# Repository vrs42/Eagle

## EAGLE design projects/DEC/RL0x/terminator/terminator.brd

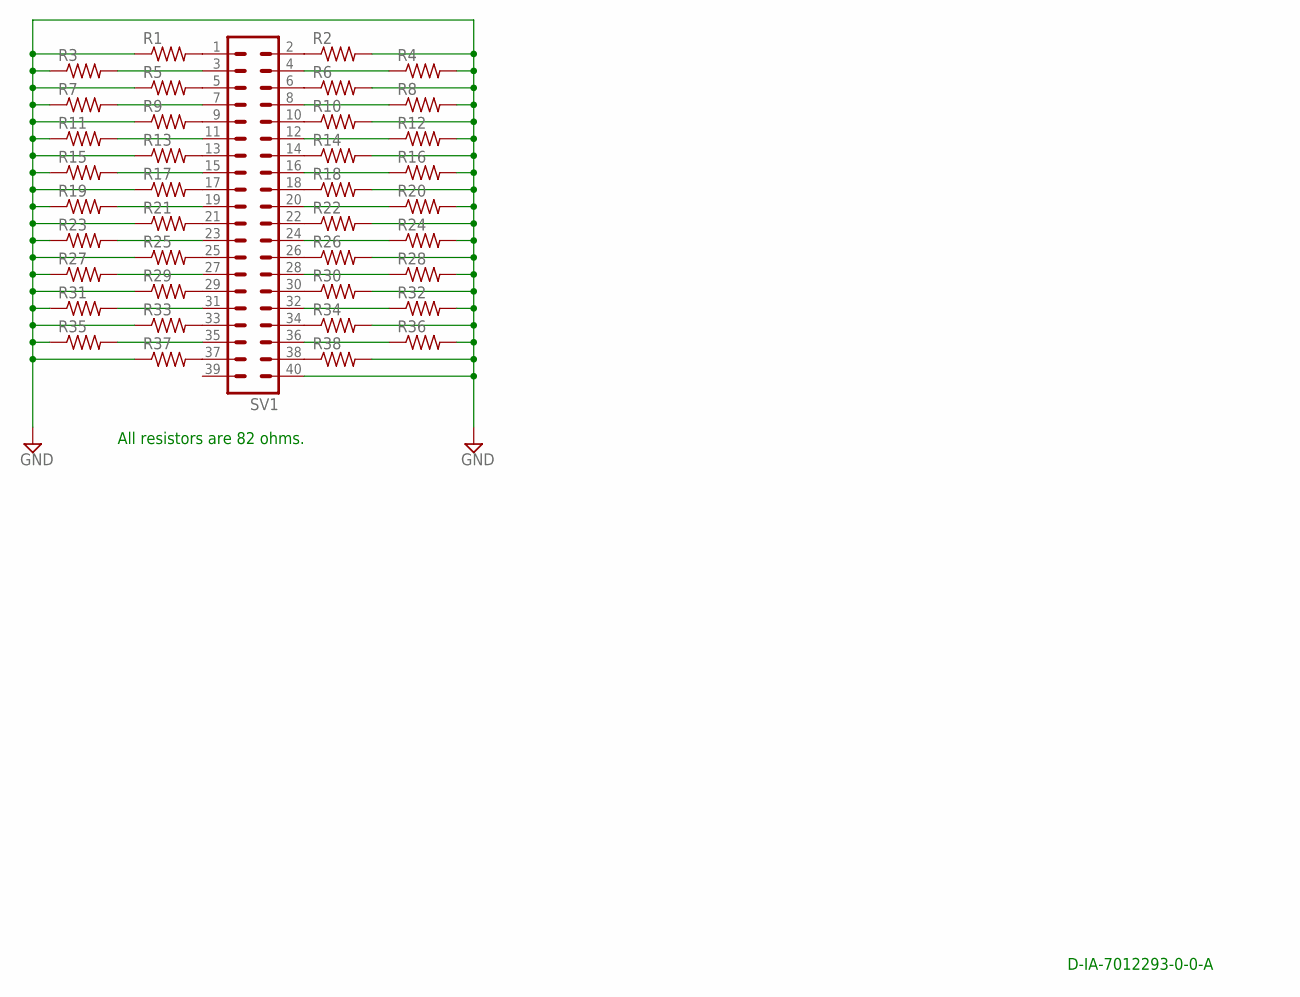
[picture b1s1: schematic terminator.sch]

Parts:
R1, R2, R3, R4, R5, R6, R7, R8, R9, R10, R11, R12, R13, R14, R15, R16, R17, R18, R19, R20, R21, R22, R23, R24, R25, R26, R27, R28, R29, R30, R31, R32, R33, R34, R35, R36, R37, R38: R-US_M0805; M0805
SV1: MA20-2

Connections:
GND: R1.1, R2.2, R3.1, R4.2, R5.1, R6.2, R7.1, R8.2, R9.1, R10.2, R11.1, R12.2, R13.1, R14.2, R15.1, R16.2, R17.1, R18.2, R19.1, R20.2, R21.1, R22.2, R23.1, R24.2, R25.1, R26.2, R27.1, R28.2, R29.1, R30.2, R31.1, R32.2, R33.1, R34.2, R35.1, R36.2, R37.1, R38.2, SV1.40
unnamed: R1.2, SV1.1
unnamed: R2.1, SV1.2
unnamed: R5.2, SV1.5
unnamed: R6.1, SV1.6
unnamed: R9.2, SV1.9
unnamed: R10.1, SV1.10
unnamed: R13.2, SV1.13
unnamed: R14.1, SV1.14
unnamed: R17.2, SV1.17
unnamed: R18.1, SV1.18
unnamed: R21.2, SV1.21
unnamed: R22.1, SV1.22
unnamed: R25.2, SV1.25
unnamed: R26.1, SV1.26
unnamed: R29.2, SV1.29
unnamed: R30.1, SV1.30
unnamed: R33.2, SV1.33
unnamed: R34.1, SV1.34
unnamed: R37.2, SV1.37
unnamed: R38.1, SV1.38
unnamed: R3.2, SV1.3
unnamed: R7.2, SV1.7
unnamed: R11.2, SV1.11
unnamed: R15.2, SV1.15
unnamed: R19.2, SV1.19
unnamed: R23.2, SV1.23
unnamed: R27.2, SV1.27
unnamed: R31.2, SV1.31
unnamed: R35.2, SV1.35
unnamed: R36.1, SV1.36
unnamed: R32.1, SV1.32
unnamed: R28.1, SV1.28
unnamed: R24.1, SV1.24
unnamed: R20.1, SV1.20
unnamed: R16.1, SV1.16
unnamed: R12.1, SV1.12
unnamed: R8.1, SV1.8
unnamed: R4.1, SV1.4

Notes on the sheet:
All resistors are 82 ohms.
D-IA-7012293-0-0-A

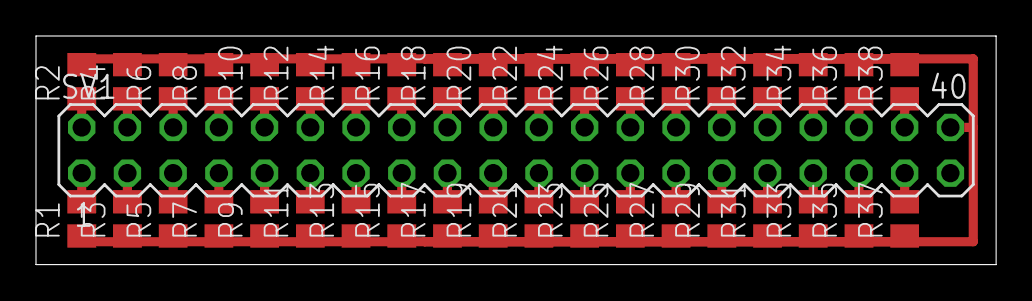
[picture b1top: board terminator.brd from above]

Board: 2 copper layers, 53.3 x 12.7 mm, 39 parts (0 on the bottom side), 39 nets.

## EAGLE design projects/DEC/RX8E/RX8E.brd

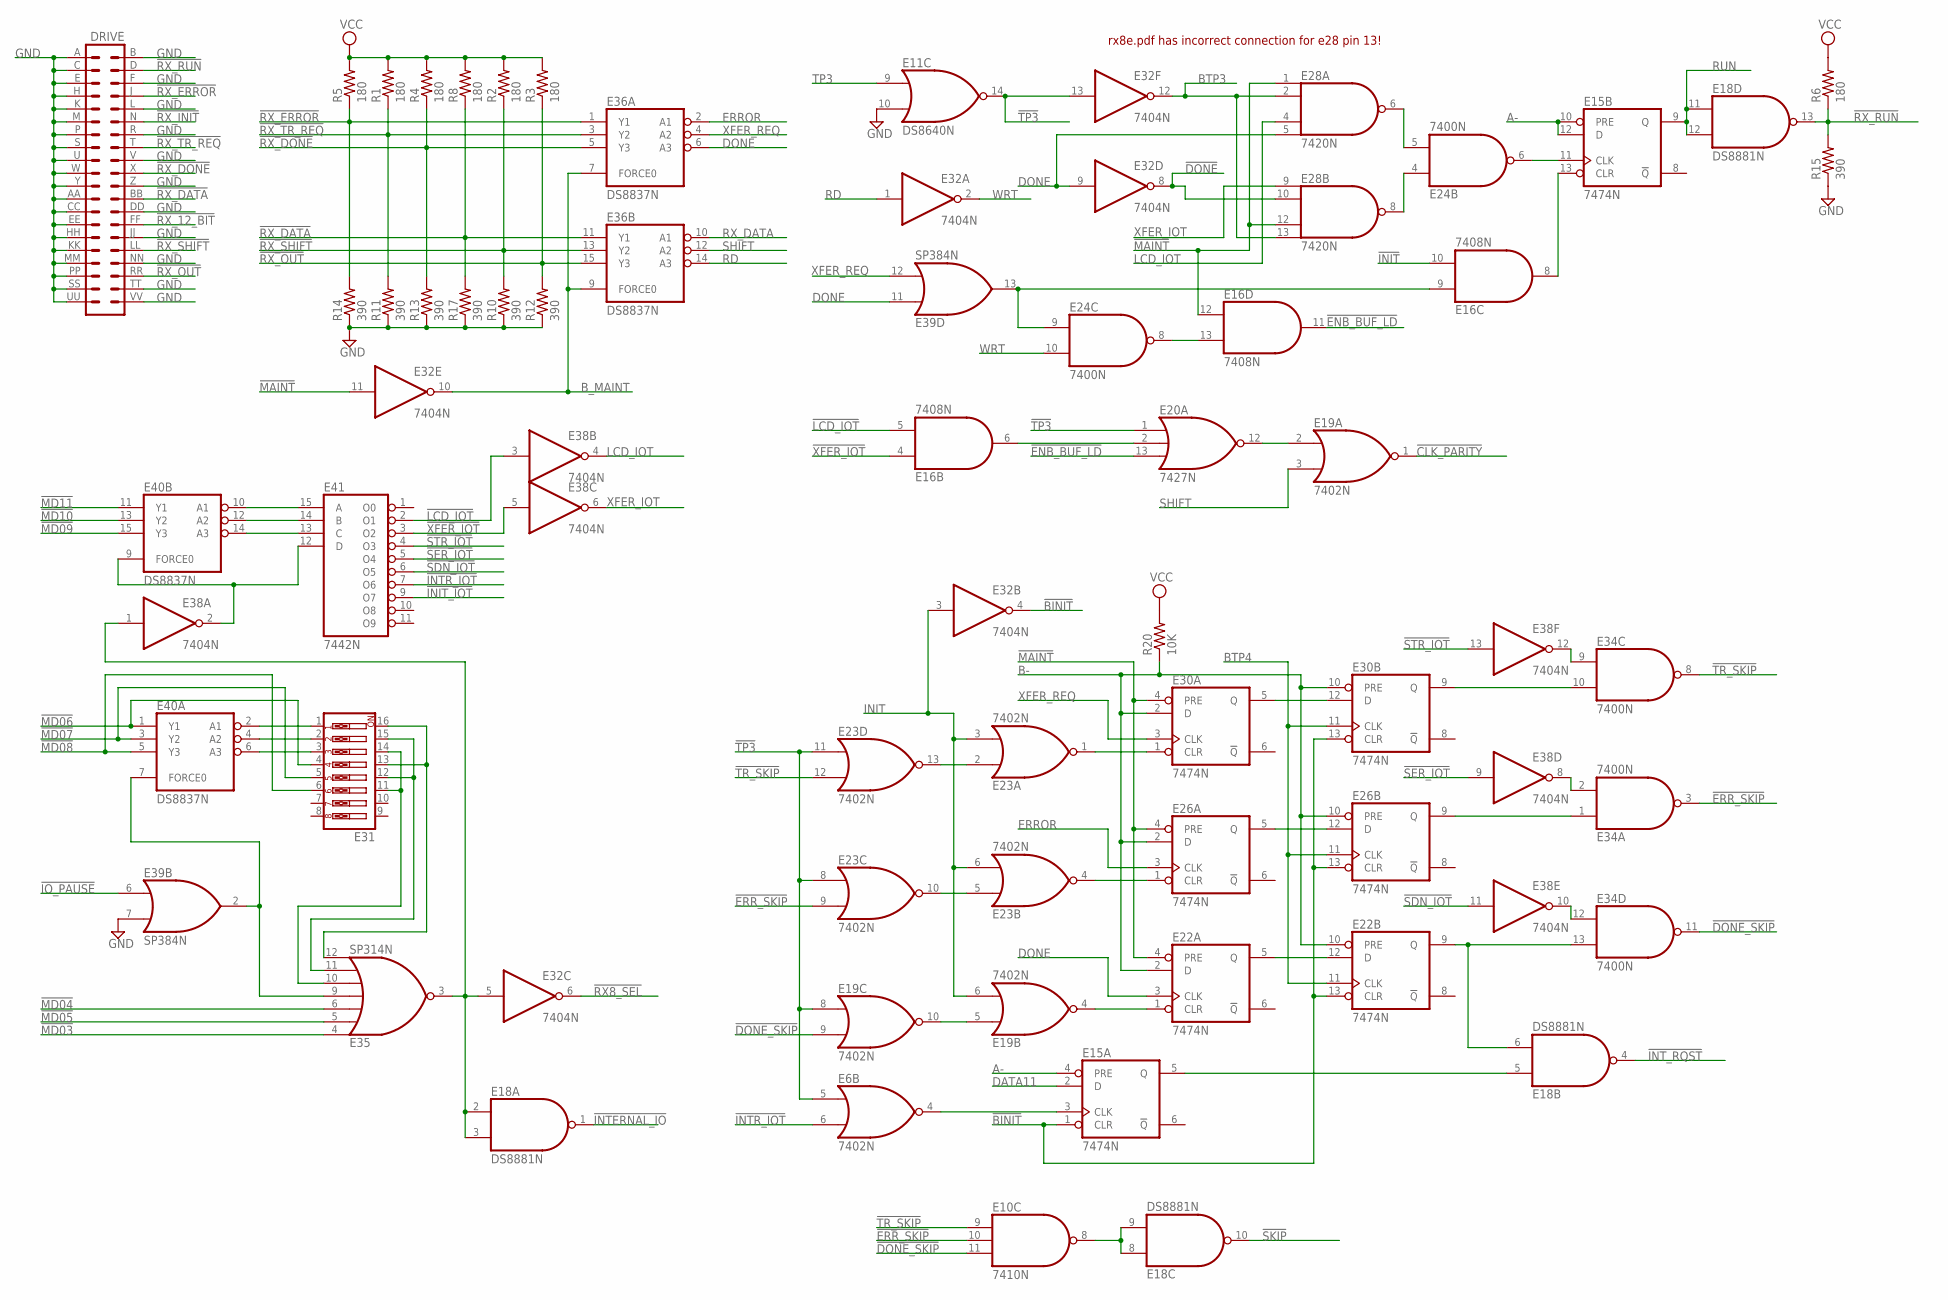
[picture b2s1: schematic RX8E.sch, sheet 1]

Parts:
DRIVE: DEC40PINH
E6, E19, E23: 7402N; DIL14
E10: 7410N; DIL14
E11: DS8640N; DIL14
E15, E22, E26, E30: 7474N; DIL14
E16: 7408N; DIL14
E18: DS8881N; DIL14
E20: 7427N; DIL14
E24, E34: 7400N; DIL14
E28: 7420N; DIL14
E31: SW_DIP-8; EDG-08
E32, E38: 7404N; DIL14
E35: SP314N; DIL14
E36, E40: DS8837N; DIL16
E39: SP384N; DIL14
E41: 7442N; DIL16
R1, R2, R3, R4, R5, R6, R8: 180; 0207/10
R10, R11, R12, R13, R14, R15, R17: 390; 0207/10
R20: 10K; 0207/10

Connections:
!BINIT: E15.1 (CLR), E22.13 (CLR), E26.13 (CLR), E30.13 (CLR), E32.4 (O)
!CLK_PARITY: E19.1 (O); also elsewhere on the board
!DONE: E28.10 (I1), E32.8 (O); also elsewhere on the board
!DONE_SKIP: E10.11 (I2), E19.9 (I1), E34.11 (O); also elsewhere on the board
!ENB_BUF_LD: E16.11 (O), E20.13 (I2); also elsewhere on the board
!ERR_SKIP: E10.10 (I1), E23.9 (I1), E34.3 (O)
!INIT: E16.10 (I1); also elsewhere on the board
!INIT_IOT: E41.9 (O7); also elsewhere on the board
!INTERNAL_IO: E18.1 (O); also elsewhere on the board
!INTR_IOT: E6.6 (I1), E41.7 (O6)
!INT_RQST: E18.4 (O); also elsewhere on the board
!IO_PAUSE: E39.6 (I0); also elsewhere on the board
!LCD_IOT: E16.5 (I1), E38.3 (I), E41.2 (O1); also elsewhere on the board
!MAINT: E16.12 (I0), E22.4 (PRE), E26.4 (PRE), E28.1 (I0), E28.12 (I2), E30.4 (PRE), E32.11 (I); also elsewhere on the board
!MD03: E35.4 (I0); also elsewhere on the board
!MD04: E35.6 (I2); also elsewhere on the board
!MD05: E35.5 (I1); also elsewhere on the board
!MD06: E31.4, E40.1 (Y1); also elsewhere on the board
!MD07: E31.5, E40.3 (Y2); also elsewhere on the board
!MD08: E31.6, E40.5 (Y3); also elsewhere on the board
!MD09: E40.15 (Y3); also elsewhere on the board
!MD10: E40.13 (Y2); also elsewhere on the board
!MD11: E40.11 (Y1); also elsewhere on the board
!RX8_SEL: E32.6 (O); also elsewhere on the board
!RX_12_BIT: DRIVE.FF (28); also elsewhere on the board
!RX_DATA: DRIVE.BB (24), E36.11 (Y1), R8.1, R17.2; also elsewhere on the board
!RX_DONE: DRIVE.X (20), E36.5 (Y3), R4.1, R13.2
!RX_ERROR: DRIVE.J (8), E36.1 (Y1), R5.1, R14.2
!RX_INIT: DRIVE.N (12); also elsewhere on the board
!RX_OUT: DRIVE.RR (36), E36.15 (Y3), R3.1, R12.2
!RX_RUN: DRIVE.D (4), E18.13 (O), R6.1, R15.2
!RX_SHIFT: DRIVE.LL (32), E36.13 (Y2), R2.1, R10.2
!RX_TR_REQ: DRIVE.T (16), E36.3 (Y2), R1.1, R11.2
!SDN_IOT: E38.11 (I), E41.6 (O5)
!SER_IOT: E38.9 (I), E41.5 (O4)
!SKIP: E18.10 (O); also elsewhere on the board
!STR_IOT: E38.13 (I), E41.4 (O3)
!TP3: E6.5 (I0), E11.14 (O), E19.8 (I0), E20.1 (I0), E23.8 (I0), E23.11 (I0), E32.13 (I); also elsewhere on the board
!TR_SKIP: E10.9 (I0), E23.12 (I1), E34.8 (O); also elsewhere on the board
!XFER_IOT: E16.4 (I0), E38.5 (I), E41.3 (O2); also elsewhere on the board
A-: E15.4 (PRE), E15.10 (PRE), E15.12 (D); also elsewhere on the board
B-: E22.2 (D), E22.10 (PRE), E26.2 (D), E26.10 (PRE), E30.2 (D), E30.10 (PRE), R20.1; also elsewhere on the board
BTP3: E28.2 (I1), E28.13 (I3), E32.12 (O); also elsewhere on the board
BTP4: E22.11 (CLK), E26.11 (CLK), E30.11 (CLK); also elsewhere on the board
B_MAINT: E32.10 (O), E36.7 (FORCE0), E36.9 (FORCE0)
DATA11: E15.2 (D); also elsewhere on the board
DONE: E22.3 (CLK), E28.5 (I3), E32.9 (I), E36.6 (A3), E39.11 (I0); also elsewhere on the board
ERROR: E26.3 (CLK), E36.2 (A1)
GND: DRIVE.A (1), DRIVE.AA (23), DRIVE.B (2), DRIVE.C (3), DRIVE.CC (25), DRIVE.DD (26), DRIVE.E (5), DRIVE.EE (27), DRIVE.F (6), DRIVE.H (7), DRIVE.HH (29), DRIVE.JJ (30), DRIVE.K (9), DRIVE.KK (31), DRIVE.L (10), DRIVE.M (11), DRIVE.MM (33), DRIVE.NN (34), DRIVE.P (13), DRIVE.PP (35), DRIVE.R (14), DRIVE.S (15), DRIVE.SS (37), DRIVE.TT (38), DRIVE.U (17), DRIVE.UU (39), DRIVE.V (18), DRIVE.VV (40), DRIVE.W (19), DRIVE.Y (21), DRIVE.Z (22), E6.7 (GND), E10.7 (GND), E11.1 (GND), E11.10 (I1), E15.7 (GND), E16.7 (GND), E18.7 (GND), E19.7 (GND), E20.7 (GND), E22.7 (GND), E23.7 (GND), E24.7 (GND), E26.7 (GND), E28.7 (GND), E30.7 (GND), E32.7 (GND), E34.7 (GND), E35.1 (GND), E36.8 (GND), E38.7 (GND), E39.1 (GND), E39.7 (I1), E40.8 (GND), E41.8 (GND), R10.1, R11.1, R12.1, R13.1, R14.1, R15.1, R17.1; also elsewhere on the board
INIT: E19.6 (I1), E23.3 (I1), E23.6 (I1), E32.3 (I); also elsewhere on the board
LCD_IOT: E28.4 (I2), E38.4 (O); also elsewhere on the board
unnamed: E31.11, E31.14, E35.10 (I4)
unnamed: E31.12, E31.15, E35.11 (I5)
unnamed: E31.13, E31.16, E35.12 (I6)
unnamed: E31.3, E40.6 (A3)
unnamed: E31.2, E40.4 (A2)
unnamed: E31.1, E40.2 (A1)
unnamed: E35.9 (I3), E39.2 (O), E40.7 (FORCE0)
unnamed: E18.2 (I0), E18.3 (I1), E32.5 (I), E35.3 (O), E38.1 (I)
unnamed: E19.5 (I0), E19.10 (O)
unnamed: E38.2 (O), E40.9 (FORCE0), E41.12 (D)
unnamed: E40.14 (A3), E41.13 (C)
unnamed: E40.12 (A2), E41.14 (B)
unnamed: E40.10 (A1), E41.15 (A)
unnamed: E19.4 (O), E22.1 (CLR)
unnamed: E23.4 (O), E26.1 (CLR)
unnamed: E23.5 (I0), E23.10 (O)
unnamed: E23.2 (I0), E23.13 (O)
unnamed: E23.1 (O), E30.1 (CLR)
unnamed: E30.5 (Q), E30.12 (D)
unnamed: E26.5 (Q), E26.12 (D)
unnamed: E22.5 (Q), E22.12 (D)
unnamed: E18.6 (I1), E22.9 (Q), E34.13 (I1)
unnamed: E26.9 (Q), E34.1 (I0)
unnamed: E6.4 (O), E15.3 (CLK)
unnamed: E30.9 (Q), E34.10 (I1)
unnamed: E34.2 (I1), E38.8 (O)
unnamed: E34.12 (I0), E38.10 (O)
unnamed: E34.9 (I0), E38.12 (O)
unnamed: E15.5 (Q), E18.5 (I0)
unnamed: E10.8 (O), E18.8 (I0), E18.9 (I1)
unnamed: E24.5 (I1), E28.6 (O)
unnamed: E16.6 (O), E20.2 (I1)
unnamed: E24.4 (I0), E28.8 (O)
unnamed: E16.9 (I0), E24.9 (I0), E39.13 (O)
unnamed: E16.13 (I1), E24.8 (O)
unnamed: E15.13 (CLR), E16.8 (O)
unnamed: E19.2 (I0), E20.12 (O)
unnamed: E15.11 (CLK), E24.6 (O)
RD: E32.1 (I), E36.14 (A3); also elsewhere on the board
RUN: E15.9 (Q), E18.11 (I0), E18.12 (I1); also elsewhere on the board
RX_DATA: E36.10 (A1); also elsewhere on the board
SHIFT: E19.3 (I1), E36.12 (A2)
TP3: E11.9 (I0); also elsewhere on the board
VCC: E6.14 (VCC), E10.14 (VCC), E11.8 (VCC), E15.14 (VCC), E16.14 (VCC), E18.14 (VCC), E19.14 (VCC), E20.14 (VCC), E22.14 (VCC), E23.14 (VCC), E24.14 (VCC), E26.14 (VCC), E28.14 (VCC), E30.14 (VCC), E32.14 (VCC), E34.14 (VCC), E35.8 (VCC), E36.16 (VCC), E38.14 (VCC), E39.8 (VCC), E40.16 (VCC), E41.16 (VCC), R1.2, R2.2, R3.2, R4.2, R5.2, R6.2, R8.2, R20.2; also elsewhere on the board
WRT: E24.10 (I1), E32.2 (O); also elsewhere on the board
XFER_IOT: E28.9 (I0), E38.6 (O); also elsewhere on the board
XFER_REQ: E30.3 (CLK), E36.4 (A2), E39.12 (I1)

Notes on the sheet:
rx8e.pdf has incorrect connection for e28 pin 13!

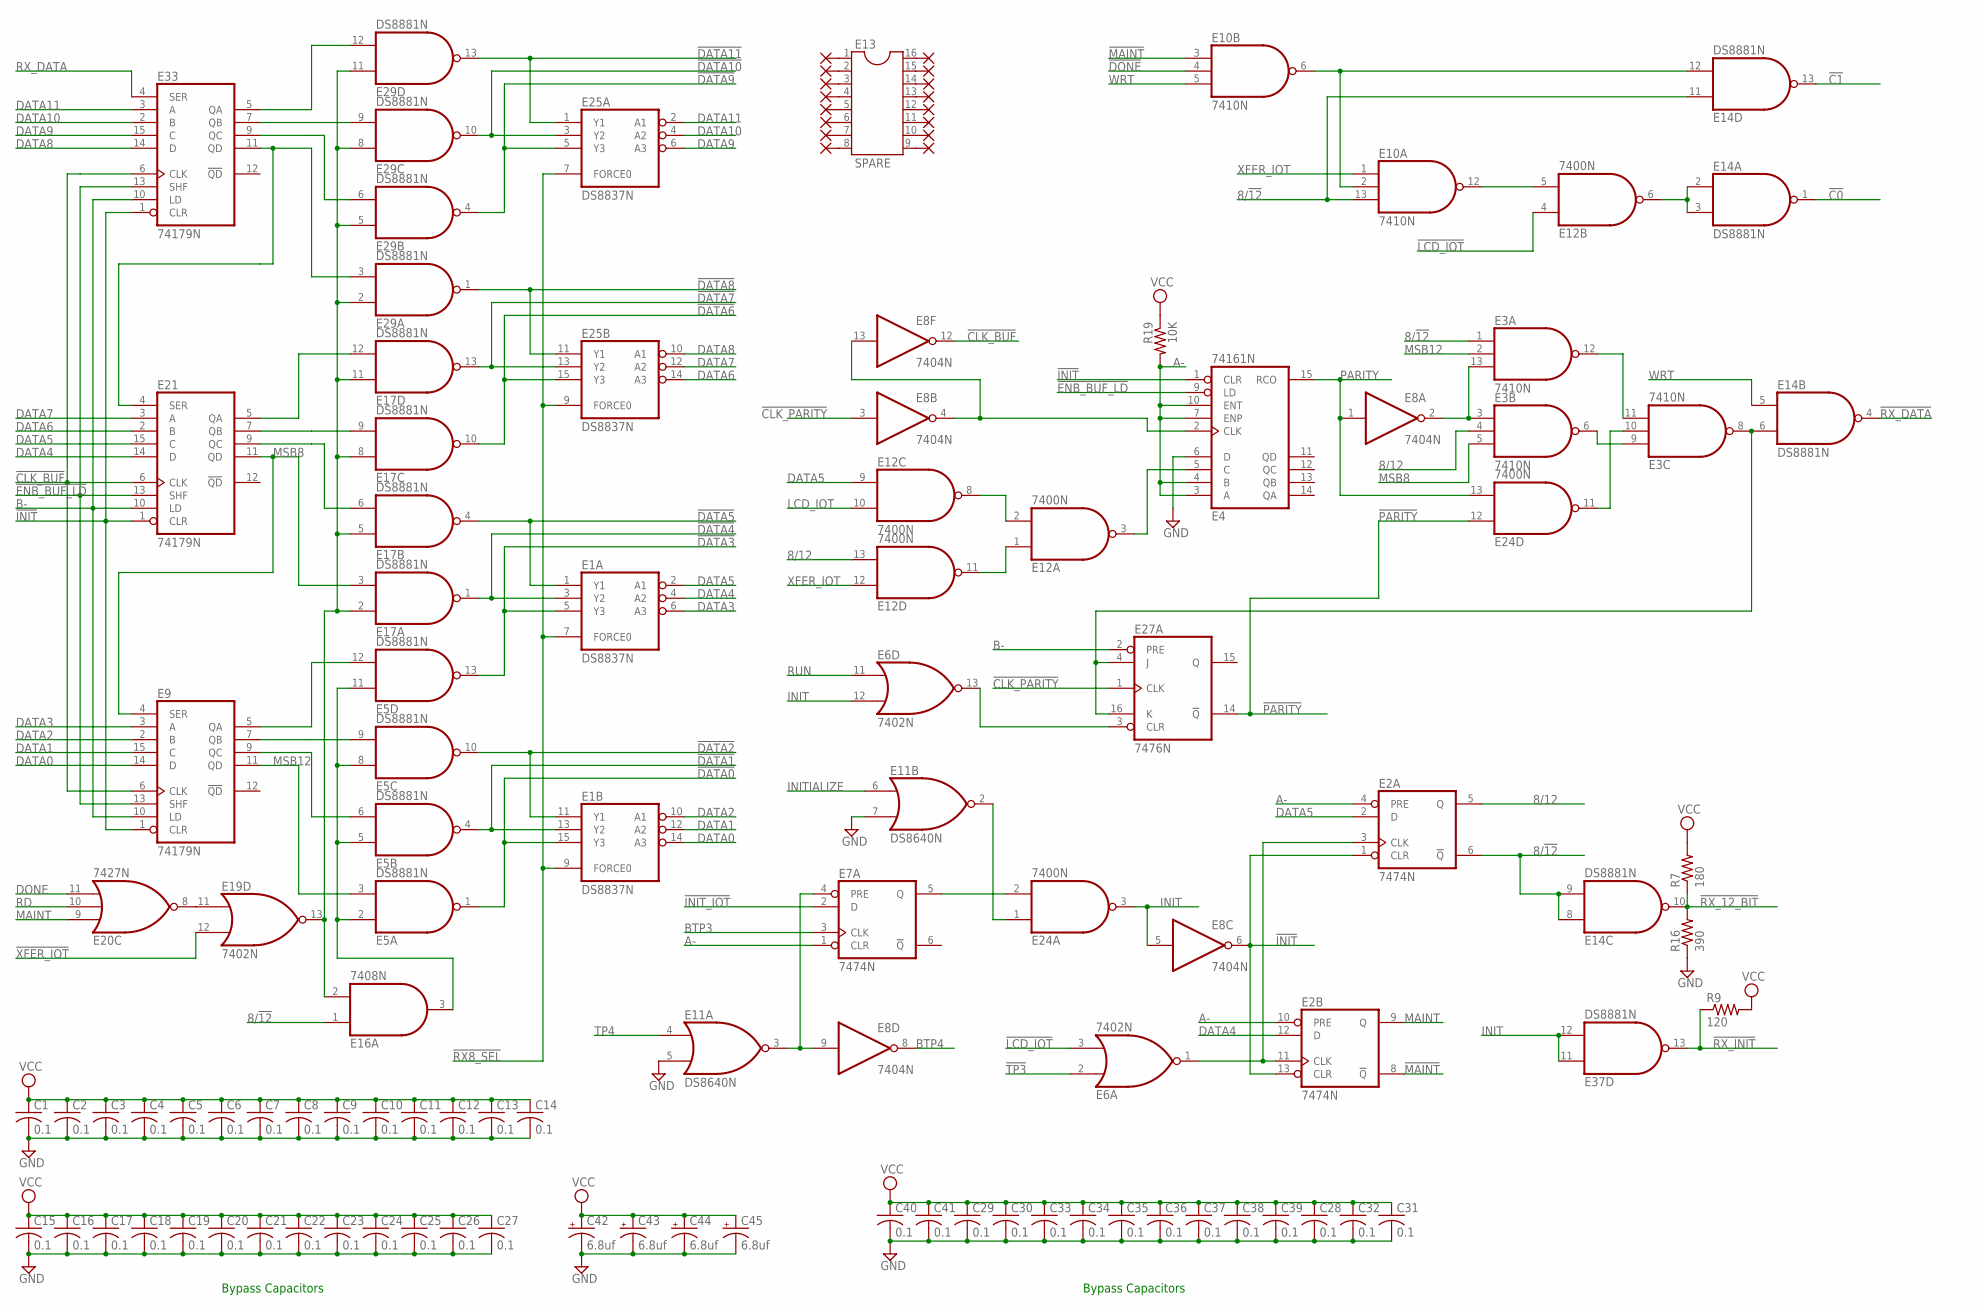
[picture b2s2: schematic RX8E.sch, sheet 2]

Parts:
C1, C2, C3, C4, C5, C6, C7, C8, C9, C10, C11, C12, C13, C14, C15, C16, C17, C18, C19, C20, C21, C22, C23, C24, C25, C26, C27, C28, C29, C30, C31, C32, C33, C34, C35, C36, C37, C38, C39, C40, C41: 0.1; C050-025X075
C42, C43, C44, C45: 6.8uf; E22-6
E1, E25: DS8837N; DIL16
E2, E7: 7474N; DIL14
E3, E10: 7410N; DIL14
E4: 74161N; DIL16
E5, E14, E17, E29, E37: DS8881N; DIL14
E6, E19: 7402N; DIL14
E8: 7404N; DIL14
E9, E21, E33: 74179N; DIL16
E11: DS8640N; DIL14
E12, E24: 7400N; DIL14
E13: SPARE; DIL16
E16: 7408N; DIL14
E20: 7427N; DIL14
E27: 7476N; DIL16
PAD10, PAD11, PAD12, PAD13, PAD14, PAD15, PAD16, PAD17, PAD20, PAD21, PAD22, PAD23, PAD24, PAD25, PAD26, PAD27: 1,6/0,8
R7: 180; 0207/10
R9: 120; 0207/10
R16: 390; 0207/10
R19: 10K; 0207/10

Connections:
8/12: E2.5 (Q), E3.4 (I1), E12.13 (I1)
8/!12: E2.6 (!Q), E3.1 (I0), E10.13 (I2), E14.8 (I0), E14.9 (I1), E14.11 (I0), E16.1 (I0)
!C0: E14.1 (O); also elsewhere on the board
!C1: E14.13 (O); also elsewhere on the board
!CLK_BUF: E8.12 (O), E9.6 (CLK), E21.6 (CLK), E33.6 (CLK)
!CLK_PARITY: E8.3 (I), E27.1 (CLK); also elsewhere on the board
!DATA0: E1.15 (Y3), E5.1 (O); also elsewhere on the board
!DATA1: E1.13 (Y2), E5.4 (O); also elsewhere on the board
!DATA2: E1.11 (Y1), E5.10 (O); also elsewhere on the board
!DATA3: E1.5 (Y3), E5.13 (O); also elsewhere on the board
!DATA4: E1.3 (Y2), E17.1 (O); also elsewhere on the board
!DATA5: E1.1 (Y1), E17.4 (O); also elsewhere on the board
!DATA6: E17.10 (O), E25.15 (Y3); also elsewhere on the board
!DATA7: E17.13 (O), E25.13 (Y2); also elsewhere on the board
!DATA8: E25.11 (Y1), E29.1 (O); also elsewhere on the board
!DATA9: E25.5 (Y3), E29.4 (O); also elsewhere on the board
!DATA10: E25.3 (Y2), E29.10 (O); also elsewhere on the board
!DATA11: E25.1 (Y1), E29.13 (O); also elsewhere on the board
!DONE: E10.4 (I1); also elsewhere on the board
!ENB_BUF_LD: E4.9 (LD), E9.13 (SHF), E21.13 (SHF), E33.13 (SHF); also elsewhere on the board
!INIT: E2.1 (CLR), E2.13 (CLR), E4.1 (CLR), E8.6 (O), E9.1 (CLR), E21.1 (CLR), E33.1 (CLR); also elsewhere on the board
!INIT_IOT: E7.2 (D); also elsewhere on the board
!LCD_IOT: E6.3 (I1), E12.4 (I0); also elsewhere on the board
!MAINT: E2.8 (!Q), E10.3 (I0); also elsewhere on the board
!PARITY: E24.12 (I0), E27.14 (!Q)
!RX8_SEL: E1.7 (FORCE0), E1.9 (FORCE0), E25.7 (FORCE0), E25.9 (FORCE0); also elsewhere on the board
!RX_12_BIT: E14.10 (O), R7.1, R16.2; also elsewhere on the board
!RX_DATA: E14.4 (O); also elsewhere on the board
!RX_INIT: E37.13 (O), R9.1; also elsewhere on the board
!TP3: E6.2 (I0); also elsewhere on the board
!XFER_IOT: E19.12 (I1); also elsewhere on the board
A-: E2.4 (PRE), E2.10 (PRE), E4.3 (A), E4.4 (B), E4.7 (ENP), E4.10 (ENT), E7.1 (CLR), R19.2; also elsewhere on the board
B-: E9.10 (LD), E21.10 (LD), E27.2 (PRE), E33.10 (LD); also elsewhere on the board
BTP3: E7.3 (CLK); also elsewhere on the board
BTP4: E8.8 (O); also elsewhere on the board
DATA0: E1.14 (A3), E9.14 (D)
DATA1: E1.12 (A2), E9.15 (C)
DATA2: E1.10 (A1), E9.2 (B)
DATA3: E1.6 (A3), E9.3 (A)
DATA4: E1.4 (A2), E2.12 (D), E21.14 (D)
DATA5: E1.2 (A1), E2.2 (D), E12.9 (I0), E21.15 (C)
DATA6: E21.2 (B), E25.14 (A3)
DATA7: E21.3 (A), E25.12 (A2)
DATA8: E25.10 (A1), E33.14 (D)
DATA9: E25.6 (A3), E33.15 (C)
DATA10: E25.4 (A2), E33.2 (B)
DATA11: E25.2 (A1), E33.3 (A); also elsewhere on the board
DONE: E20.11 (I2); also elsewhere on the board
GND: C1.2, C2.2, C3.2, C4.2, C5.2, C6.2, C7.2, C8.2, C9.2, C10.2, C11.2, C12.2, C13.2, C14.2, C15.2, C16.2, C17.2, C18.2, C19.2, C20.2, C21.2, C22.2, C23.2, C24.2, C25.2, C26.2, C27.2, C28.2, C29.2, C30.2, C31.2, C32.2, C33.2, C34.2, C35.2, C36.2, C37.2, C38.2, C39.2, C40.2, C41.2, C42.-, C43.-, C44.-, C45.-, E1.8 (GND), E2.7 (GND), E3.7 (GND), E4.6 (D), E4.8 (GND), E5.7 (GND), E6.7 (GND), E7.7 (GND), E8.7 (GND), E9.8 (GND), E10.7 (GND), E11.1 (GND), E11.5 (I1), E11.7 (I1), E12.7 (GND), E14.7 (GND), E16.7 (GND), E17.7 (GND), E19.7 (GND), E20.7 (GND), E21.8 (GND), E24.7 (GND), E25.8 (GND), E27.13 (GND), E29.7 (GND), E33.8 (GND), E37.7 (GND), R16.1; also elsewhere on the board
INIT: E6.12 (I1), E8.5 (I), E24.3 (O), E37.11 (I0), E37.12 (I1); also elsewhere on the board
INITIALIZE: E11.6 (I0); also elsewhere on the board
LCD_IOT: E12.10 (I1); also elsewhere on the board
MAINT: E2.9 (Q), E20.9 (I0)
MSB8: E3.5 (I2), E9.4 (SER), E17.3 (I1), E21.11 (QD)
MSB12: E3.2 (I1), E5.3 (I1), E9.11 (QD)
unnamed: E5.9 (I1), E9.7 (QB)
unnamed: E16.2 (I1), E17.2 (I0), E17.5 (I0), E17.8 (I0), E17.11 (I0), E19.13 (O), E29.2 (I0), E29.5 (I0), E29.8 (I0), E29.11 (I0)
unnamed: E19.11 (I0), E20.8 (O)
unnamed: E5.2 (I0), E5.5 (I0), E5.8 (I0), E5.11 (I0), E16.3 (O)
unnamed: E13.1, PAD10.1
unnamed: E13.2, PAD11.1
unnamed: E13.3, PAD12.1
unnamed: E13.4, PAD13.1
unnamed: E13.5, PAD14.1
unnamed: E13.6, PAD15.1
unnamed: E13.7, PAD16.1
unnamed: E13.8, PAD17.1
unnamed: E4.5 (C), E12.3 (O)
unnamed: E12.6 (O), E14.2 (I0), E14.3 (I1)
unnamed: E13.16, PAD20.1
unnamed: E13.15, PAD21.1
unnamed: E13.14, PAD22.1
unnamed: E13.13, PAD23.1
unnamed: E13.12, PAD24.1
unnamed: E13.11, PAD25.1
unnamed: E13.10, PAD26.1
unnamed: E13.9, PAD27.1
unnamed: E21.4 (SER), E29.3 (I1), E33.11 (QD)
unnamed: E10.12 (O), E12.5 (I1)
unnamed: E5.6 (I1), E9.9 (QC)
unnamed: E10.2 (I1), E10.6 (O), E14.12 (I1)
unnamed: E12.1 (I0), E12.11 (O)
unnamed: E12.2 (I1), E12.8 (O)
unnamed: E3.3 (I0), E3.13 (I2), E8.2 (O)
unnamed: E3.11 (I2), E3.12 (O)
unnamed: E3.6 (O), E3.9 (I0)
unnamed: E3.10 (I1), E24.11 (O)
unnamed: E3.8 (O), E14.6 (I1), E27.4 (J), E27.16 (K)
unnamed: E7.4 (PRE), E8.9 (I), E11.3 (O)
unnamed: E4.2 (CLK), E8.4 (O), E8.13 (I)
unnamed: E7.5 (Q), E24.2 (I1)
unnamed: E6.13 (O), E27.3 (CLR)
unnamed: E11.2 (O), E24.1 (I0)
unnamed: E2.3 (CLK), E2.11 (CLK), E6.1 (O)
unnamed: E5.12 (I1), E9.5 (QA)
unnamed: E17.6 (I1), E21.9 (QC)
unnamed: E17.9 (I1), E21.7 (QB)
unnamed: E17.12 (I1), E21.5 (QA)
unnamed: E29.12 (I1), E33.5 (QA)
unnamed: E29.6 (I1), E33.9 (QC)
unnamed: E29.9 (I1), E33.7 (QB)
PARITY: E4.15 (RCO), E8.1 (I), E24.13 (I1); also elsewhere on the board
RD: E20.10 (I1); also elsewhere on the board
RUN: E6.11 (I0); also elsewhere on the board
RX_DATA: E33.4 (SER); also elsewhere on the board
TP4: E11.4 (I0); also elsewhere on the board
VCC: C1.1, C2.1, C3.1, C4.1, C5.1, C6.1, C7.1, C8.1, C9.1, C10.1, C11.1, C12.1, C13.1, C14.1, C15.1, C16.1, C17.1, C18.1, C19.1, C20.1, C21.1, C22.1, C23.1, C24.1, C25.1, C26.1, C27.1, C28.1, C29.1, C30.1, C31.1, C32.1, C33.1, C34.1, C35.1, C36.1, C37.1, C38.1, C39.1, C40.1, C41.1, C42.+, C43.+, C44.+, C45.+, E1.16 (VCC), E2.14 (VCC), E3.14 (VCC), E4.16 (VCC), E5.14 (VCC), E6.14 (VCC), E7.14 (VCC), E8.14 (VCC), E9.16 (VCC), E10.14 (VCC), E11.8 (VCC), E12.14 (VCC), E14.14 (VCC), E16.14 (VCC), E17.14 (VCC), E19.14 (VCC), E20.14 (VCC), E21.16 (VCC), E24.14 (VCC), E25.16 (VCC), E27.5 (VCC), E29.14 (VCC), E33.16 (VCC), E37.14 (VCC), R7.2, R9.2, R19.1; also elsewhere on the board
WRT: E10.5 (I2), E14.5 (I0); also elsewhere on the board
XFER_IOT: E10.1 (I0), E12.12 (I0); also elsewhere on the board

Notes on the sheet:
Bypass Capacitors

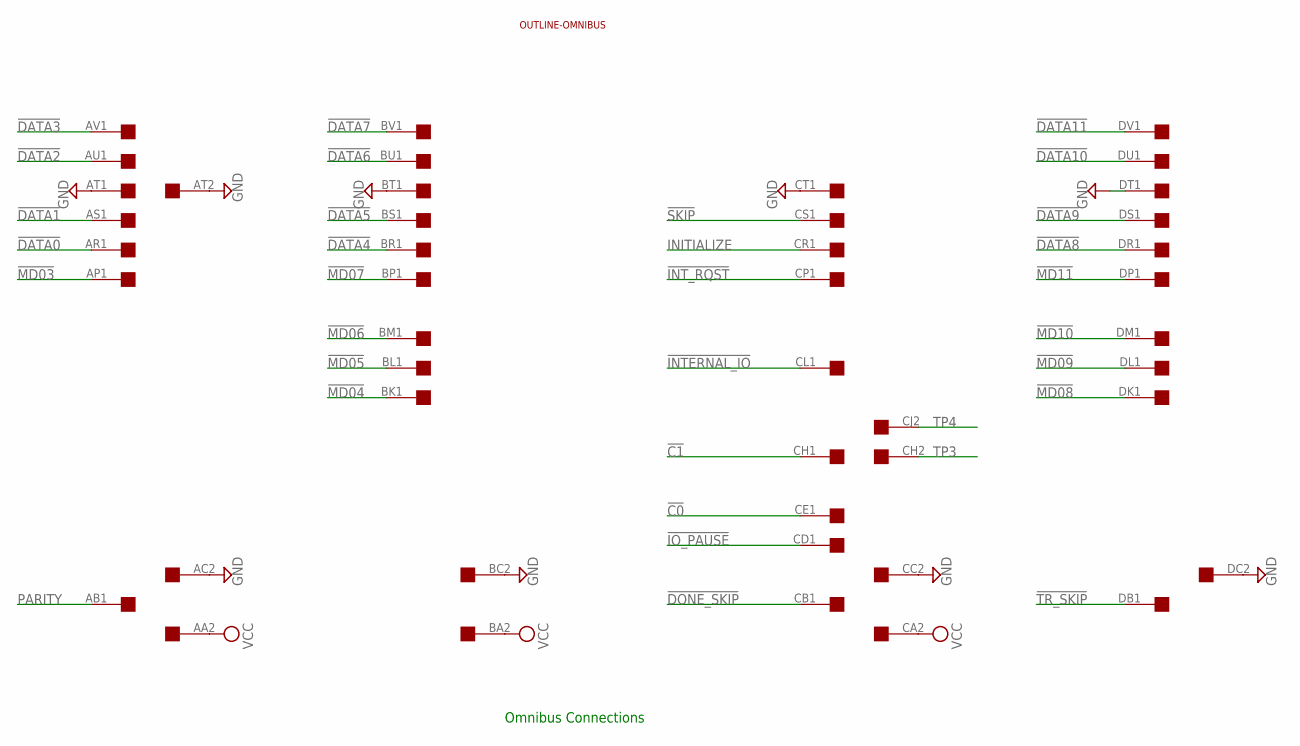
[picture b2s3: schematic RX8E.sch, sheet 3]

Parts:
U$2: QUAD; EDGE-CON8
U$5: OUTLINE-OMNIBUS; OMNIBUS

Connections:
!C0: U$2.CE1; also elsewhere on the board
!C1: U$2.CH1; also elsewhere on the board
!DATA0: U$2.AR1; also elsewhere on the board
!DATA1: U$2.AS1; also elsewhere on the board
!DATA2: U$2.AU1; also elsewhere on the board
!DATA3: U$2.AV1; also elsewhere on the board
!DATA4: U$2.BR1; also elsewhere on the board
!DATA5: U$2.BS1; also elsewhere on the board
!DATA6: U$2.BU1; also elsewhere on the board
!DATA7: U$2.BV1; also elsewhere on the board
!DATA8: U$2.DR1; also elsewhere on the board
!DATA9: U$2.DS1; also elsewhere on the board
!DATA10: U$2.DU1; also elsewhere on the board
!DATA11: U$2.DV1; also elsewhere on the board
!DONE_SKIP: U$2.CB1; also elsewhere on the board
!INTERNAL_IO: U$2.CL1; also elsewhere on the board
!INT_RQST: U$2.CP1; also elsewhere on the board
!IO_PAUSE: U$2.CD1; also elsewhere on the board
!MD03: U$2.AP1; also elsewhere on the board
!MD04: U$2.BK1; also elsewhere on the board
!MD05: U$2.BL1; also elsewhere on the board
!MD06: U$2.BM1; also elsewhere on the board
!MD07: U$2.BP1; also elsewhere on the board
!MD08: U$2.DK1; also elsewhere on the board
!MD09: U$2.DL1; also elsewhere on the board
!MD10: U$2.DM1; also elsewhere on the board
!MD11: U$2.DP1; also elsewhere on the board
!SKIP: U$2.CS1; also elsewhere on the board
!TR_SKIP: U$2.DB1; also elsewhere on the board
GND: U$2.AC2, U$2.AT1, U$2.AT2, U$2.BC2, U$2.BT1, U$2.CC2, U$2.CT1, U$2.DC2, U$2.DT1; also elsewhere on the board
INITIALIZE: U$2.CR1; also elsewhere on the board
PARITY: U$2.AB1; also elsewhere on the board
TP3: U$2.CH2; also elsewhere on the board
TP4: U$2.CJ2; also elsewhere on the board
VCC: U$2.AA2, U$2.BA2, U$2.CA2; also elsewhere on the board

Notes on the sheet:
Omnibus Connections

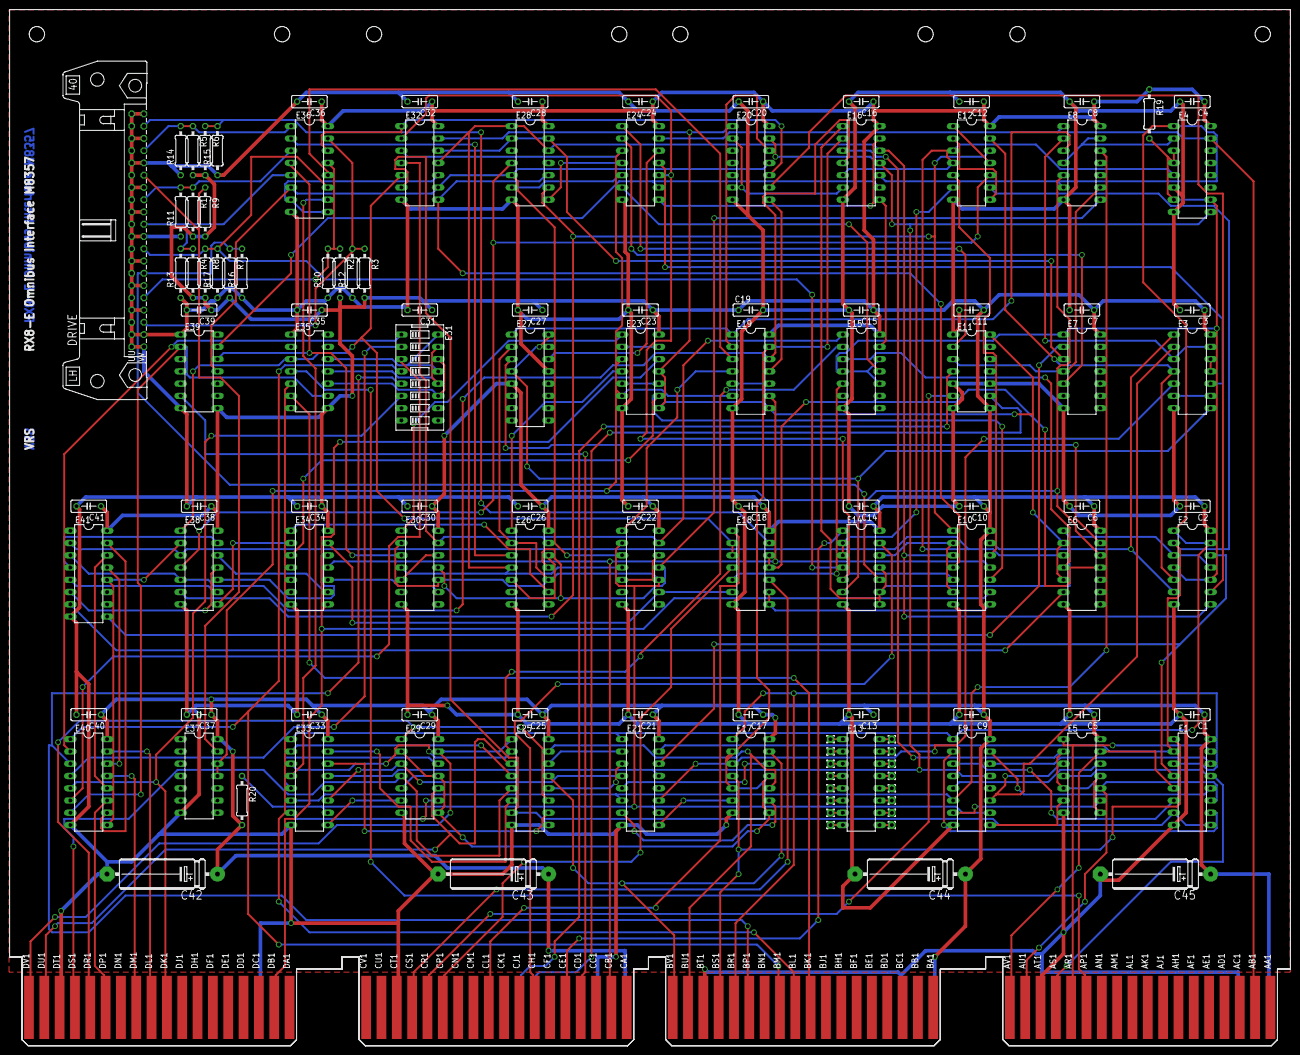
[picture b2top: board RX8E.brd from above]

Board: 2 copper layers, 265.3 x 214.6 mm, 124 parts (0 on the bottom side), 179 nets.

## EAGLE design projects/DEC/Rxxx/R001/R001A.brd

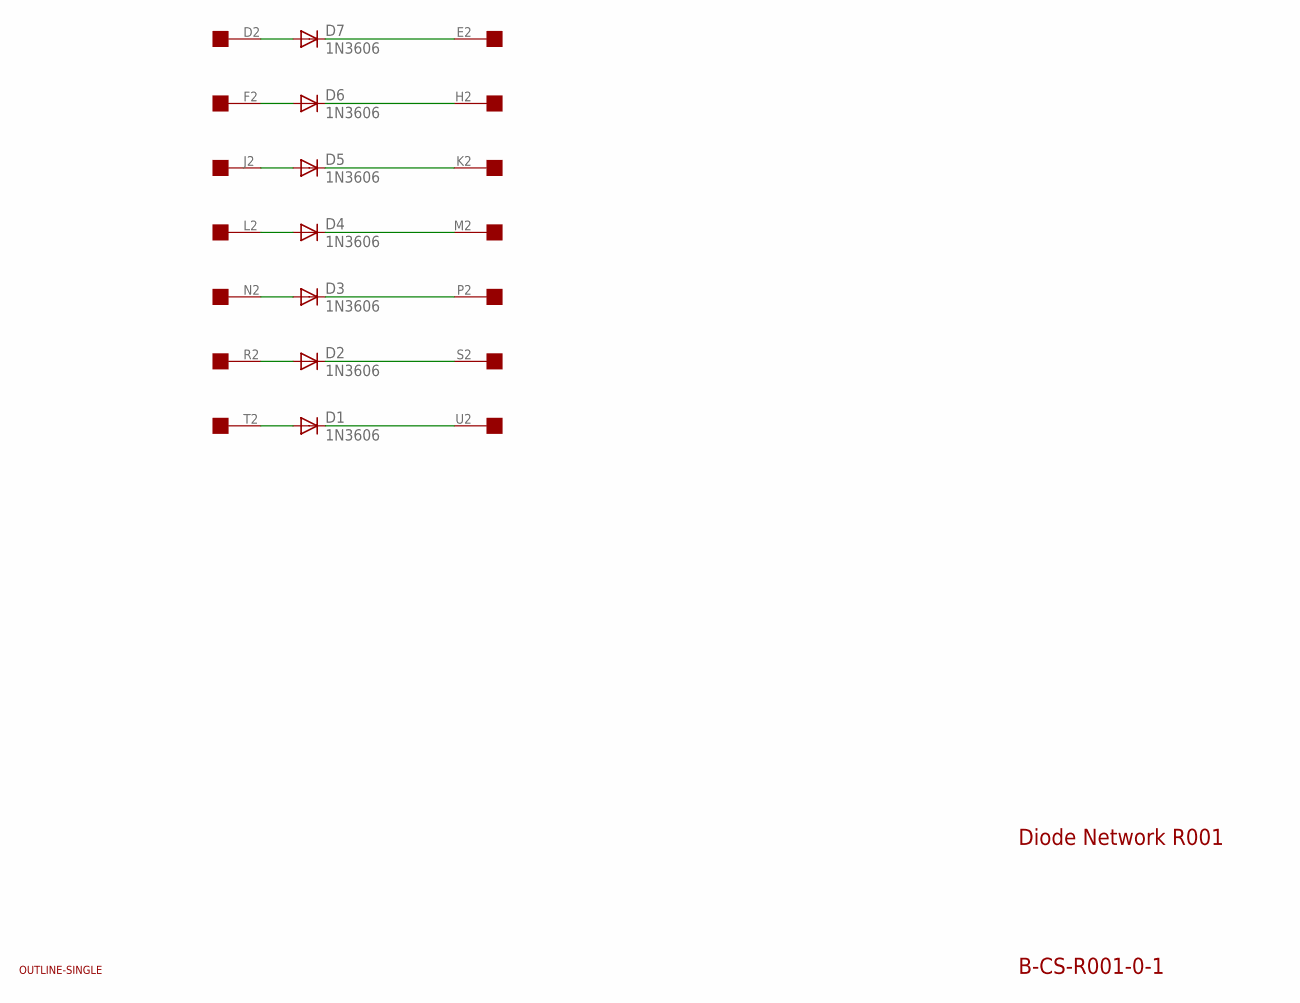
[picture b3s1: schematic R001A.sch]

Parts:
D1, D2, D3, D4, D5, D6, D7: 1N3606; DO35-10
U$1: OUTLINE-SINGLE; SINGLE
U$2: EDGE-1; EDGE-CON1

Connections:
unnamed: D7.A, U$2.D2
unnamed: D6.A, U$2.F2
unnamed: D7.C, U$2.E2
unnamed: D6.C, U$2.H2
unnamed: D4.C, U$2.M2
unnamed: D5.C, U$2.K2
unnamed: D4.A, U$2.L2
unnamed: D3.A, U$2.N2
unnamed: D3.C, U$2.P2
unnamed: D5.A, U$2.J2
unnamed: D2.A, U$2.R2
unnamed: D2.C, U$2.S2
unnamed: D1.A, U$2.T2
unnamed: D1.C, U$2.U2

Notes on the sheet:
Diode Network R001
B-CS-R001-0-1

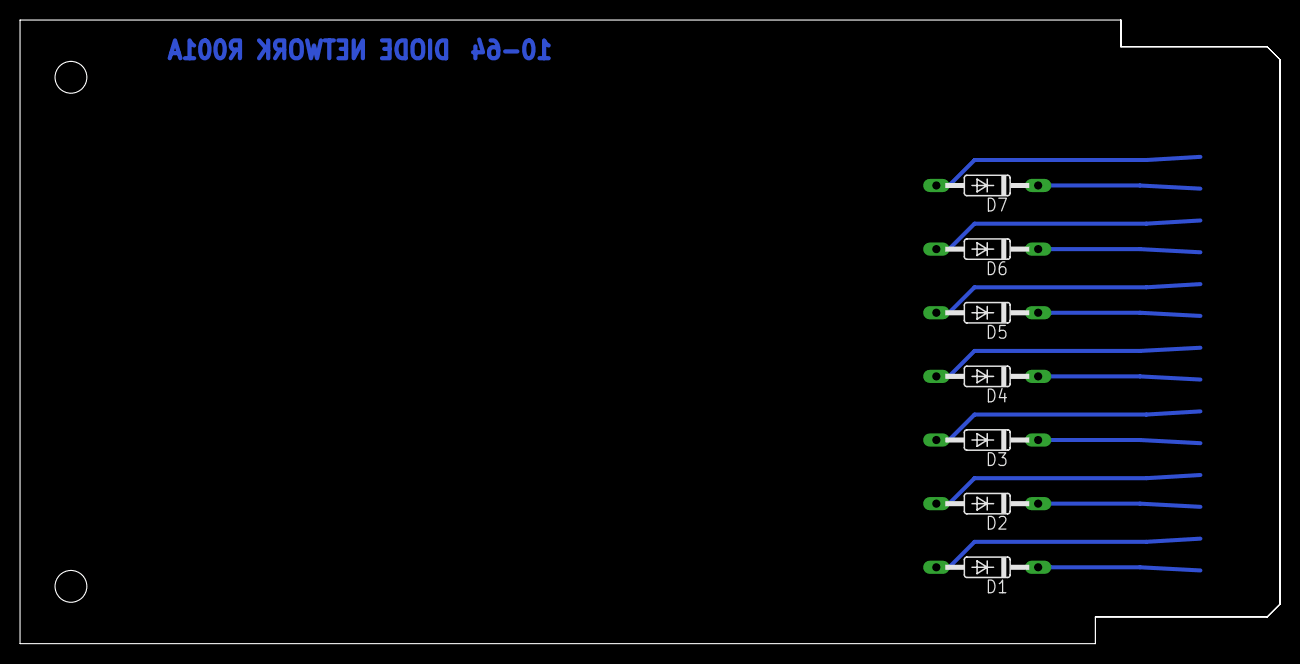
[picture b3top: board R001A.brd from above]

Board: 2 copper layers, 125.7 x 62.2 mm, 9 parts (0 on the bottom side), 14 nets.
